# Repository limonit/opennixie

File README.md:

# Open Nixie Clock
Modular Clock based on Nixie Tubes

## What is it
Open Nixie is a modular design of a clock based on Nixie tubes.

## Homepage
More can be found at:
http://open-nixie.elektrofanklub.pl/

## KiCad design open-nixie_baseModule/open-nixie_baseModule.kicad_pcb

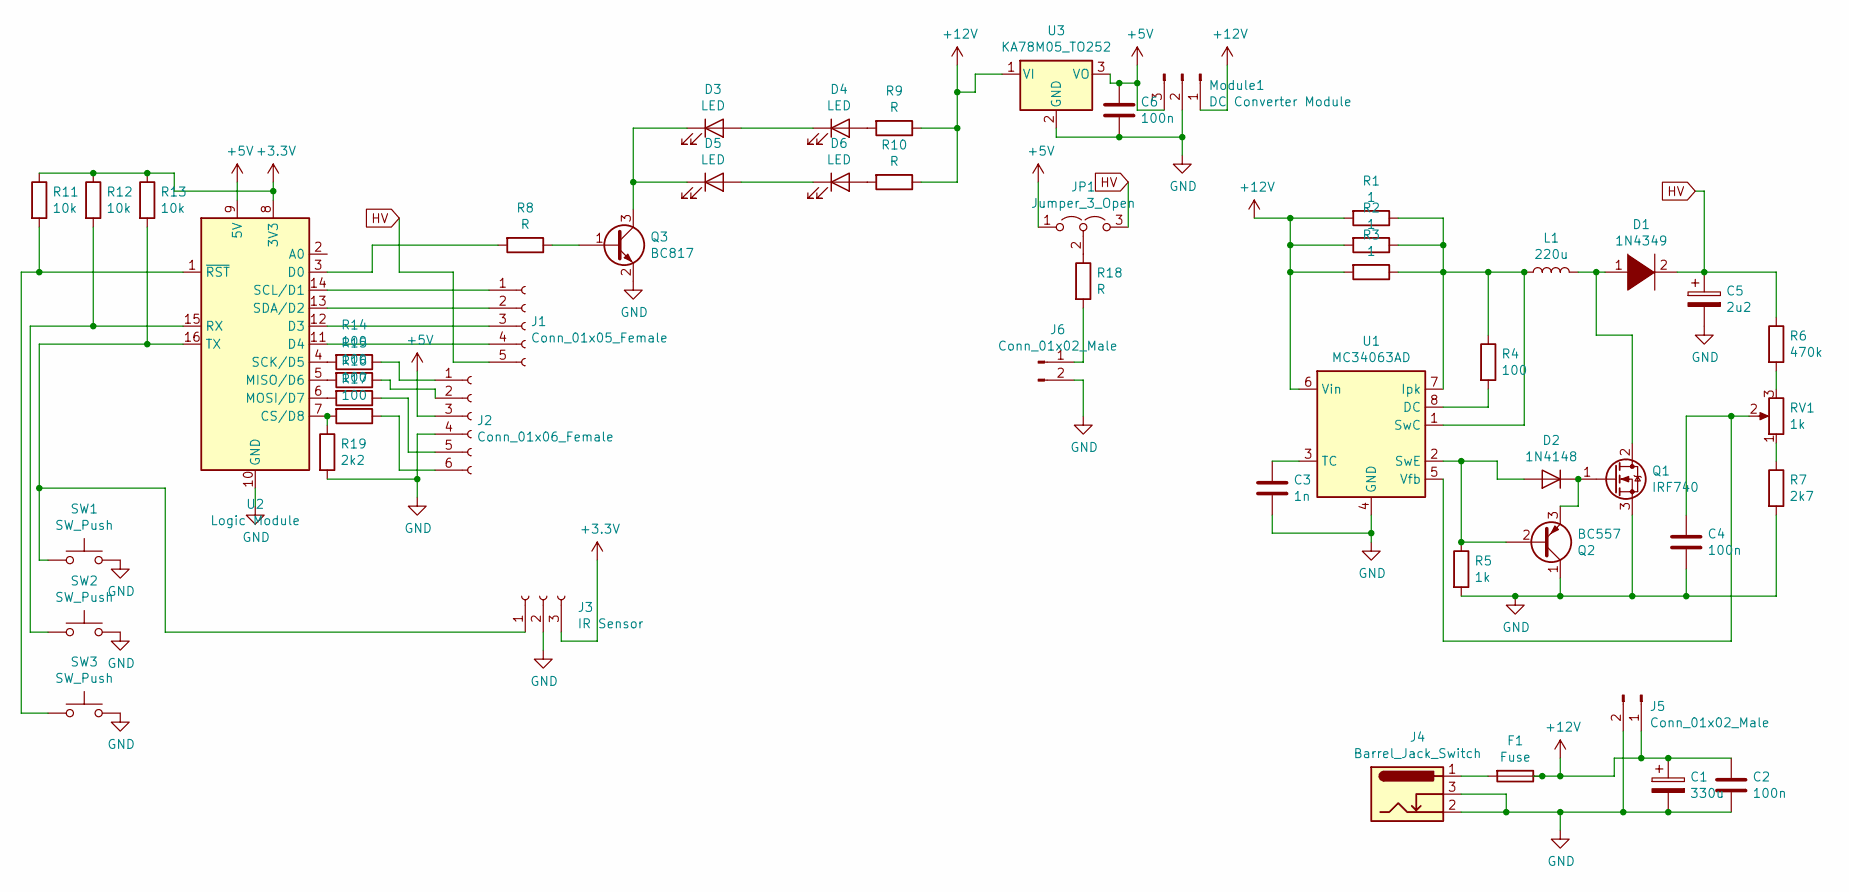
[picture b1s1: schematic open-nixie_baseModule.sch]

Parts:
C1: 330u; CP_Radial_D8.0mm_P3.80mm
C2, C4, C6: 100n; C_0805_2012Metric_Pad1.15x1.40mm_HandSolder
C3: 1n; C_0805_2012Metric_Pad1.15x1.40mm_HandSolder
C5: 2u2; CP_Radial_D8.0mm_P3.80mm
D1: 1N4349; D_DO-41_SOD81_P12.70mm_Horizontal
D2: 1N4148; D_SOD-123
D3, D4, D5, D6: LED; LED_PLCC_2835_Handsoldering
F1: Fuse; D_DO-41_SOD81_P12.70mm_Horizontal
J1: Conn_01x05_Female; PinHeader_1x05_P2.54mm_Vertical
J2: Conn_01x06_Female; PinHeader_1x06_P2.54mm_Vertical
J3: IR Sensor; PinHeader_1x03_P2.54mm_Vertical
J4: Barrel_Jack_Switch; DC_Jack_Vertical
J5, J6: Conn_01x02_Male; PinHeader_1x02_P2.54mm_Vertical
JP1: Jumper_3_Open; SolderJumper-3_P1.3mm_Open_RoundedPad1.0x1.5mm_NumberLabels
L1: 220u; Inductor_3_5
Module1: DC Converter Module; PinHeader_1x03_P2.54mm_Vertical
Q1: IRF740; TO-220-3_Horizontal_TabDown
Q2: BC557; TO-92_Inline_Wide
Q3: BC817; SOT-23_Handsoldering
R1, R2, R3: 1; R_1206_3216Metric_Pad1.42x1.75mm_HandSolder
R4, R14, R15, R16, R17: 100; R_0805_2012Metric_Pad1.15x1.40mm_HandSolder
R5: 1k; R_0805_2012Metric_Pad1.15x1.40mm_HandSolder
R6: 470k; R_0805_2012Metric_Pad1.15x1.40mm_HandSolder
R7: 2k7; R_0805_2012Metric_Pad1.15x1.40mm_HandSolder
R8, R9, R10, R18: R; R_0805_2012Metric_Pad1.15x1.40mm_HandSolder
R11, R12, R13: 10k; R_0805_2012Metric_Pad1.15x1.40mm_HandSolder
R19: 2k2; R_0805_2012Metric_Pad1.15x1.40mm_HandSolder
RV1: 1k; Potentiometer_Bourns_3266Z_Horizontal
SW1, SW2, SW3: SW_Push; SW_TH_Tactile_Omron_B3F-10xx_2pol
U1: MC34063AD; DIP-8_W7.62mm_LongPads
U2: Logic Module; wemos-d1-mini-with-pin-header-pin-correct
U3: KA78M05_TO252; TO-252-2

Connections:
+3V3: J3.3, R11.1, R12.1, R13.1, U2.8 (3V3)
+5V: C6.1, J2.3, JP1.1 (A), Module1.3, U2.9 (5V), U3.3 (VO)
+12V: C1.1, C2.1, F1.1, J5.1, Module1.1, R1.2, R2.2, R3.2, R9.1, R10.1, U1.6 (Vin), U3.1 (VI)
GND: C1.2, C2.2, C3.2, C4.2, C5.2, C6.2, J2.4, J3.2, J4.2, J4.3, J5.2, J6.2, Module1.2, Q1.3 (S), Q2.1 (C), Q3.2 (E), R5.2, R7.2, R19.2, SW1.2, SW2.2, SW3.2, U1.4 (GND), U2.10 (GND), U3.2 (GND)
HV: C5.1, D1.2 (A), J1.5, JP1.3 (B), R6.1
unnamed: C3.1, U1.3 (TC)
unnamed: C4.1, RV1.2, U1.5 (Vfb)
unnamed: D1.1 (K), L1.2, Q1.2 (D)
unnamed: D2.1 (K), Q1.1 (G), Q2.3 (E)
unnamed: D2.2 (A), Q2.2 (B), R5.1, U1.2 (SwE)
unnamed: D3.1 (K), D5.1 (K), Q3.3 (C)
unnamed: D3.2 (A), D4.1 (K)
unnamed: D4.2 (A), R9.2
unnamed: D5.2 (A), D6.1 (K)
unnamed: D6.2 (A), R10.2
unnamed: F1.2, J4.1
unnamed: J1.1, U2.14 (SCL/D1)
unnamed: J1.2, U2.13 (SDA/D2)
unnamed: J1.3, U2.12 (D3)
unnamed: J1.4, U2.11 (D4)
unnamed: J2.1, R14.1
unnamed: J2.2, R15.1
unnamed: J2.5, R16.1
unnamed: J2.6, R17.1
unnamed: J3.1, R13.2, SW1.1, U2.16 (TX)
unnamed: J6.1, R18.2
unnamed: JP1.2 (C), R18.1
unnamed: L1.1, R1.1, R2.1, R3.1, R4.1, U1.1 (SwC), U1.7 (Ipk)
unnamed: Q3.1 (B), R8.1
unnamed: R4.2, U1.8 (DC)
unnamed: R6.2, RV1.3
unnamed: R7.1, RV1.1
unnamed: R8.2, U2.3 (D0)
unnamed: R11.2, SW3.1, U2.1 (~RST)
unnamed: R12.2, SW2.1, U2.15 (RX)
unnamed: R14.2, U2.4 (SCK/D5)
unnamed: R15.2, U2.5 (MISO/D6)
unnamed: R16.2, U2.6 (MOSI/D7)
unnamed: R17.2, R19.1, U2.7 (CS/D8)

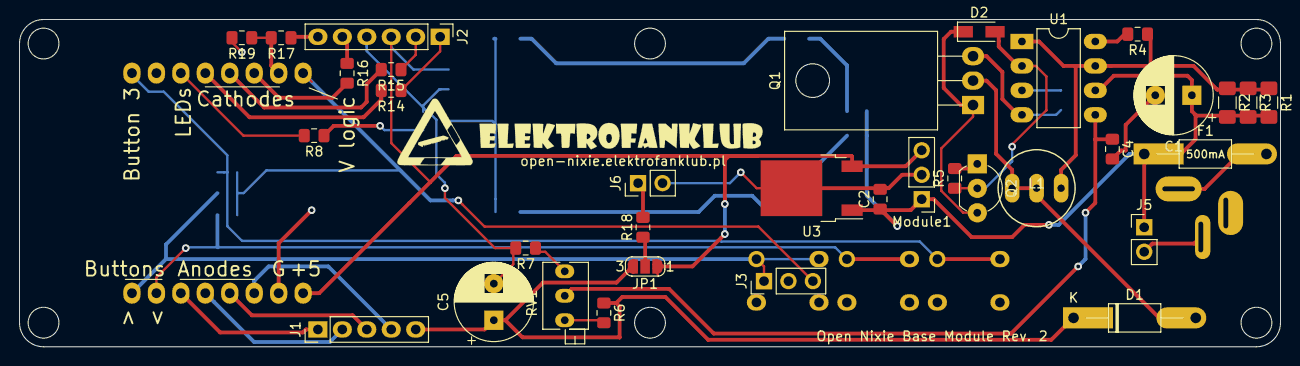
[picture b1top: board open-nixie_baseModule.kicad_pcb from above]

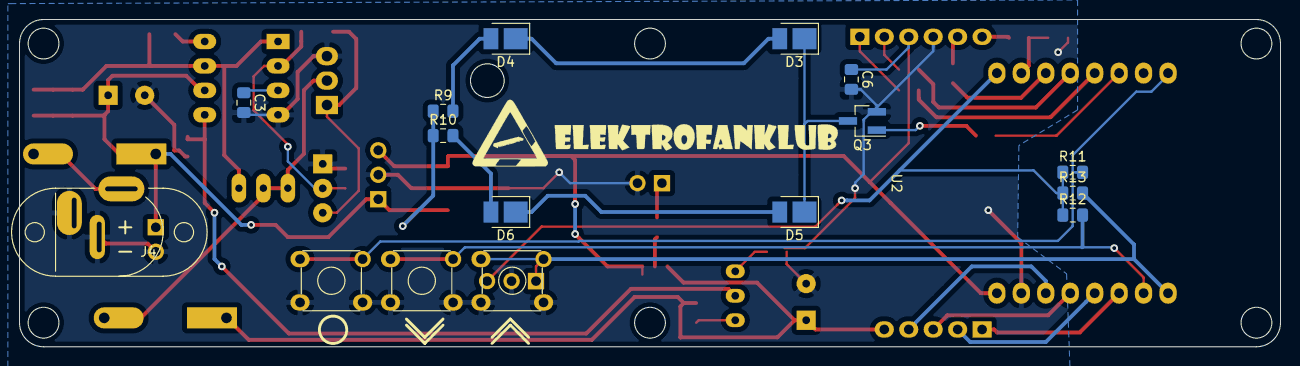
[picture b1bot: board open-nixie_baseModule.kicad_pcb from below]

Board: 2 copper layers, 131.0 x 34.0 mm, 51 parts (17 on the bottom side), 39 nets.

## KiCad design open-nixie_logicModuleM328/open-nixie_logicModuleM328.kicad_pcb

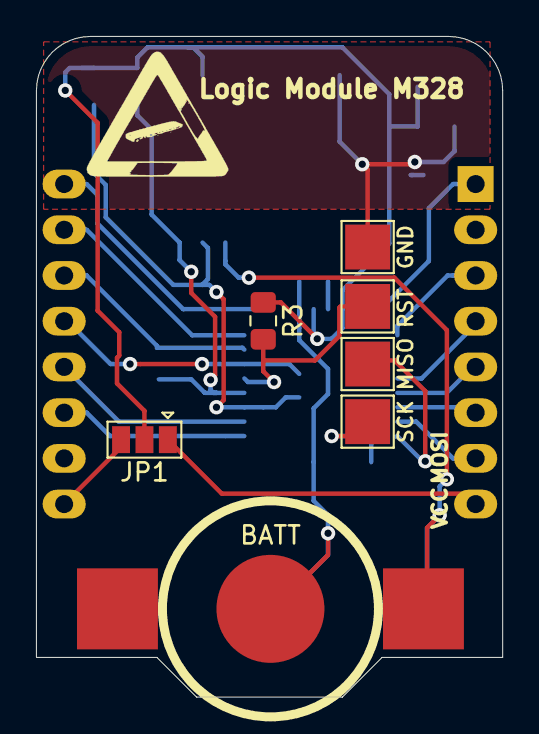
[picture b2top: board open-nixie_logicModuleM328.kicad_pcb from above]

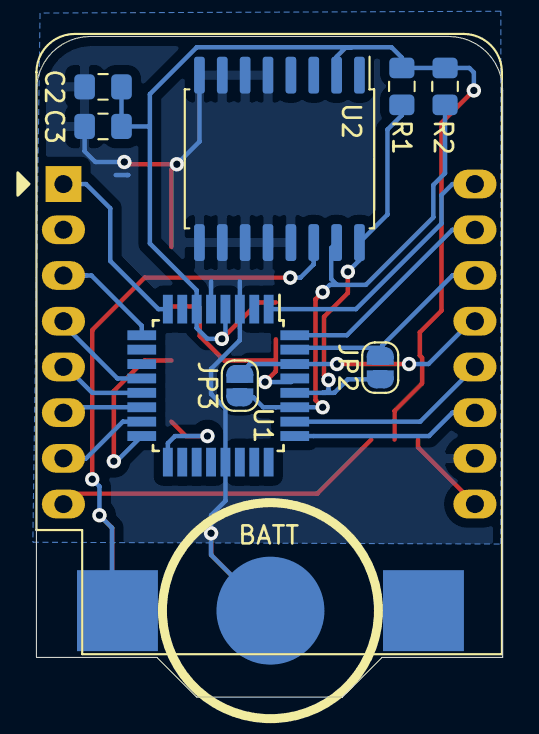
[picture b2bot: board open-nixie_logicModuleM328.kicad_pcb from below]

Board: 2 copper layers, 25.9 x 36.7 mm, 17 parts (10 on the bottom side), 22 nets.

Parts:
BATT: Battery_Cell; cr1225_battery
BATT#2: Battery_Cell; cr1225_battery
C1: WeMos_D1_mini; WEMOS_D1_mini_light
C2, C3: C; C_0805_2012Metric_Pad1.15x1.40mm_HandSolder
GND: TestPoint; TestPoint_Pad_2.5x2.5mm
JP1: Jumper_3_Open; SolderJumper-3_P1.3mm_Open_Pad1.0x1.5mm
JP2, JP3: Jumper_NO_Small; SolderJumper-2_P1.3mm_Open_RoundedPad1.0x1.5mm
MISO: TestPoint; TestPoint_Pad_2.5x2.5mm
R1, R2, R3: R; R_0805_2012Metric_Pad1.15x1.40mm_HandSolder
RST: TestPoint; TestPoint_Pad_2.5x2.5mm
SCK: TestPoint; TestPoint_Pad_2.5x2.5mm
U1: ATmega328P-AU; TQFP-32_7x7mm_P0.8mm
U2: DS3231M; SOIC-16W_7.5x10.3mm_P1.27mm

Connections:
GND: BATT.2, BATT#2.2, C1.10, C2.1, C3.1, GND.1, U1.3, U1.5, U1.21, U2.5, U2.6, U2.7, U2.8, U2.9, U2.10, U2.11, U2.12, U2.13
unnamed: BATT.1, BATT#2.1, U2.14
unnamed: C1.1, U1.8
unnamed: C1.3, U1.9
unnamed: C1.4, U1.12
unnamed: C1.5, U1.13
unnamed: C1.6, U1.14
unnamed: C1.7, U1.15
unnamed: C1.8, JP1.1
unnamed: C1.9, JP1.3
unnamed: C1.11, U1.25
unnamed: C1.12, U1.26
unnamed: C1.13, JP3.2, U1.30
unnamed: C1.14, JP2.2, U1.31
unnamed: C1.15, U1.32
unnamed: C1.16, U1.1
unnamed: JP2.1, R1.2, U1.28, U2.16
unnamed: JP3.1, R2.2, U1.27, U2.15
unnamed: R3.2, RST.1, U1.29
unnamed: MISO.1, U1.16
unnamed: SCK.1, U1.17
VCC: C2.2, C3.2, JP1.2, R1.1, R2.1, R3.1, U1.4, U1.6, U2.2

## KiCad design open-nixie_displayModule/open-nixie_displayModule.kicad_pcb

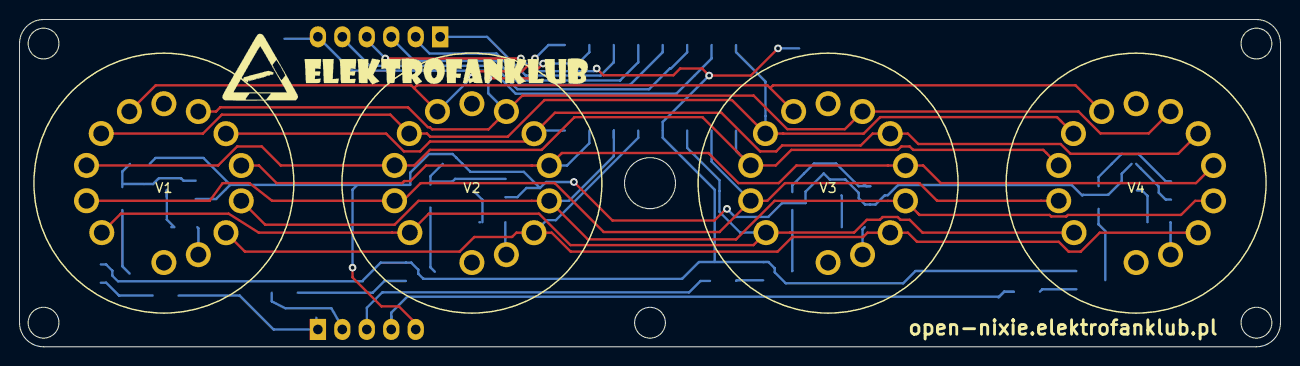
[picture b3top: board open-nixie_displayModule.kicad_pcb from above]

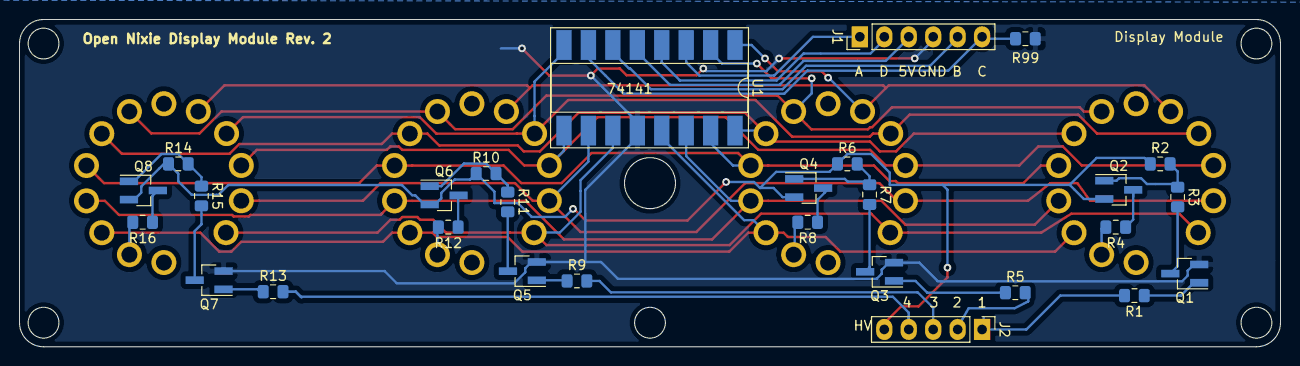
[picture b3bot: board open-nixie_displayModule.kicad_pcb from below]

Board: 2 copper layers, 131.0 x 34.0 mm, 32 parts (28 on the bottom side), 41 nets.

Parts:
J1: Conn_01x06_Male; PinHeader_1x06_P2.54mm_Vertical
J2: Conn_01x05_Male; PinHeader_1x05_P2.54mm_Vertical
Q1, Q3, Q5, Q7: MMBTA42; SOT-23_Handsoldering
Q2, Q4, Q6, Q8: MMBTA92; SOT-23_Handsoldering
R1, R5, R9, R13: 33k; R_0805_2012Metric_Pad1.15x1.40mm_HandSolder
R2, R6, R10, R14: 100k; R_0805_2012Metric_Pad1.15x1.40mm_HandSolder
R3, R7, R11, R15: 470k; R_0805_2012Metric_Pad1.15x1.40mm_HandSolder
R4, R8, R12, R16: 10k; R_0805_2012Metric_Pad1.15x1.40mm_HandSolder
R99: 2k2; R_0805_2012Metric_Pad1.15x1.40mm_HandSolder
U1: 74141; DIP-16_W8.89mm_SMDSocket_LongPads
V1, V2, V3, V4: LC513; LC-513

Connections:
/A1: R4.2, V1.A
/A2: R8.2, V2.A
/A3: R12.2, V3.A
/A4: R16.2, V4.A
/C1: U1.11, V1.1, V2.1, V3.1, V4.1
/C2: U1.10, V1.2, V2.2, V3.2, V4.2
/C3: U1.9, V1.3, V2.3, V3.3, V4.3
/C4: U1.8, V1.4, V2.4, V3.4, V4.4
/C5: U1.1, V1.5, V2.5, V3.5, V4.5
/C6: U1.2, V1.6, V2.6, V3.6, V4.6
/C7: U1.16, V1.7, V2.7, V3.7, V4.7
/C8: U1.15, V1.8, V2.8, V3.8, V4.8
/C9: U1.14, V1.9, V2.9, V3.9, V4.9
/C10: U1.13, V1.0, V2.0, V3.0, V4.0
GND: J1.4, Q1.2, Q3.2, Q5.2, Q7.2, R99.2, U1.12
unnamed: J1.1, U1.3
unnamed: J1.2, U1.4
unnamed: J1.5, U1.6
unnamed: J1.6, R99.1, U1.7
unnamed: J2.1, R1.2
unnamed: J2.2, R5.2
unnamed: J2.3, R9.2
unnamed: J2.4, R13.2
unnamed: J2.5, Q2.2, Q4.2, Q6.2, Q8.2, R2.1, R6.1, R10.1, R14.1
unnamed: Q1.1, R1.1
unnamed: Q1.3, R3.2
unnamed: Q2.1, R2.2, R3.1
unnamed: Q2.3, R4.1
unnamed: Q3.1, R5.1
unnamed: Q3.3, R7.2
unnamed: Q4.1, R6.2, R7.1
unnamed: Q4.3, R8.1
unnamed: Q5.1, R9.1
unnamed: Q5.3, R11.2
unnamed: Q6.1, R10.2, R11.1
unnamed: Q6.3, R12.1
unnamed: Q7.1, R13.1
unnamed: Q7.3, R15.2
unnamed: Q8.1, R14.2, R15.1
unnamed: Q8.3, R16.1
VCC: J1.3, U1.5

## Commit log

2021-03-14 initial
2021-03-14 Clean up
2023-11-18 Raspberry Pi Pico code
    Raspberry Pi Pico code
    Version of Open Nixie clock that uses Rapberry Pi Pico W. Rather PoC than a project.
    Simple, straightforward implementation that uses NTP. Not very optimized, lot of code taken directly from Pi Pico examples. Yet working proof of concept.
